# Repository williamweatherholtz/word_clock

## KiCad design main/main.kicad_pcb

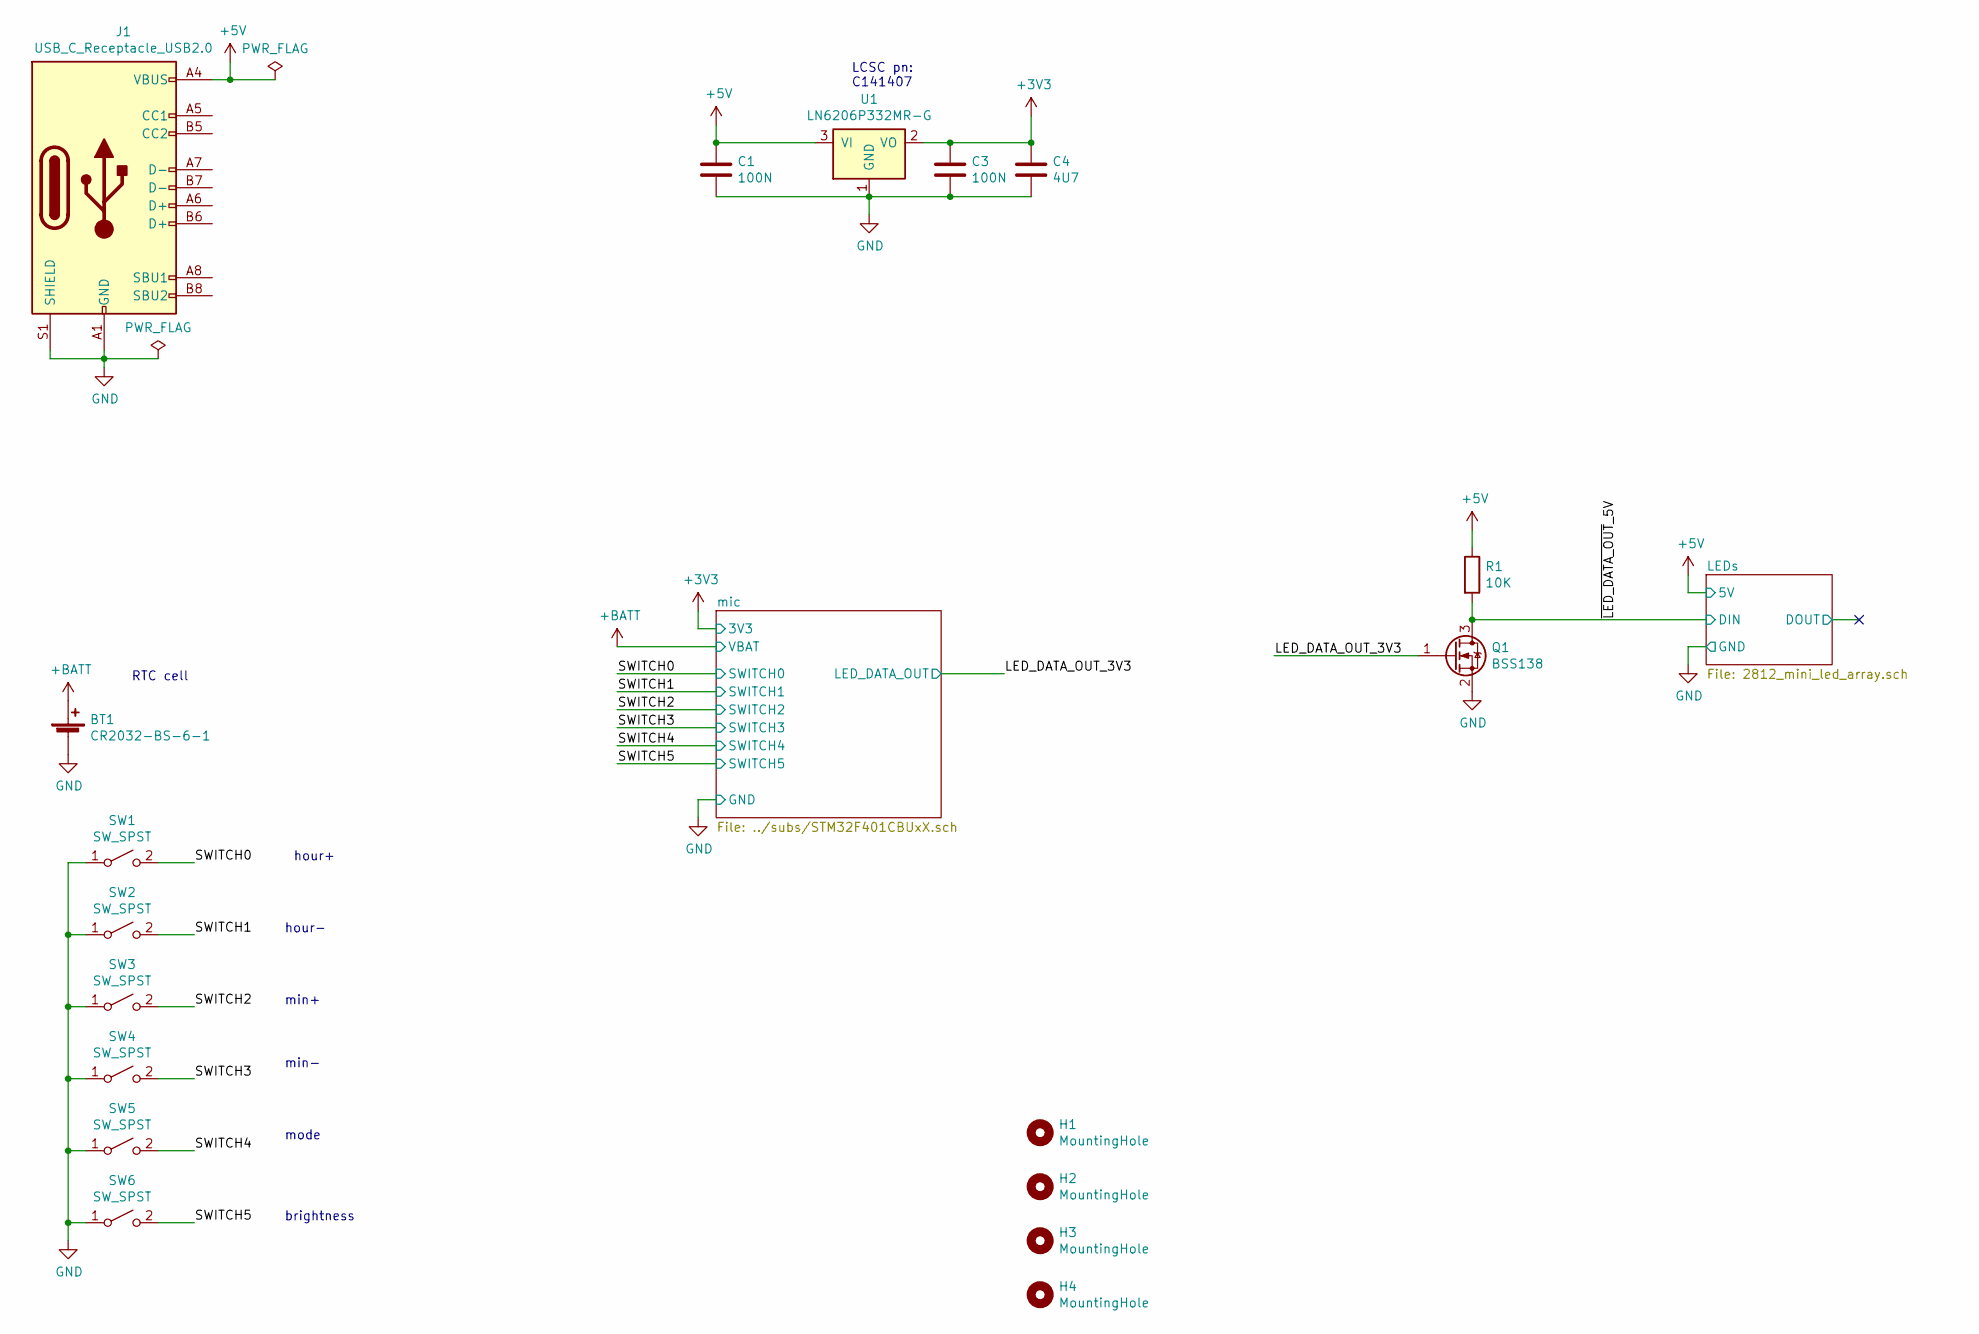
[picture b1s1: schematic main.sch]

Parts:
BT1: CR2032-BS-6-1
C1, C3: 100N; C_0402_1005Metric
C4: 4U7; C_0402_1005Metric
H1, H2, H3, H4: MountingHole; MountingHole_2.1mm
J1: USB_C_Receptacle_USB2.0; C168688
Q1: BSS138; SOT-23
R1: 10K; R_0402_1005Metric
SW1, SW2, SW3, SW4, SW5, SW6: SW_SPST; KAN4562-0501C
U1: LN6206P332MR-G; SOT-23

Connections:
+3V3: C3.1, C4.1, U1.2 (VO); also elsewhere on the board
+5V: C1.1, J1.A4 (VBUS), J1.A9 (VBUS), J1.B4 (VBUS), J1.B9 (VBUS), R1.1, U1.3 (VI); also elsewhere on the board
+BATT: BT1.1 (+); also elsewhere on the board
/LED_DATA_OUT_3V3: Q1.1 (G); also elsewhere on the board
/SWITCH0: SW1.2 (B); also elsewhere on the board
/SWITCH1: SW2.2 (B); also elsewhere on the board
/SWITCH2: SW3.2 (B); also elsewhere on the board
/SWITCH3: SW4.2 (B); also elsewhere on the board
/SWITCH4: SW5.2 (B); also elsewhere on the board
/SWITCH5: SW6.2 (B); also elsewhere on the board
/~LED_DATA_OUT~_5V: Q1.3 (D), R1.2; also elsewhere on the board
GND: BT1.2 (-), C1.2, C3.2, C4.2, J1.A1 (GND), J1.A12 (GND), J1.B1 (GND), J1.B12 (GND), J1.S1 (SHIELD), Q1.2 (S), SW1.1 (A), SW2.1 (A), SW3.1 (A), SW4.1 (A), SW5.1 (A), SW6.1 (A), U1.1 (GND); also elsewhere on the board

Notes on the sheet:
hour+
min+
mode
brightness
hour-
min-
LCSC pn: C141407
RTC cell

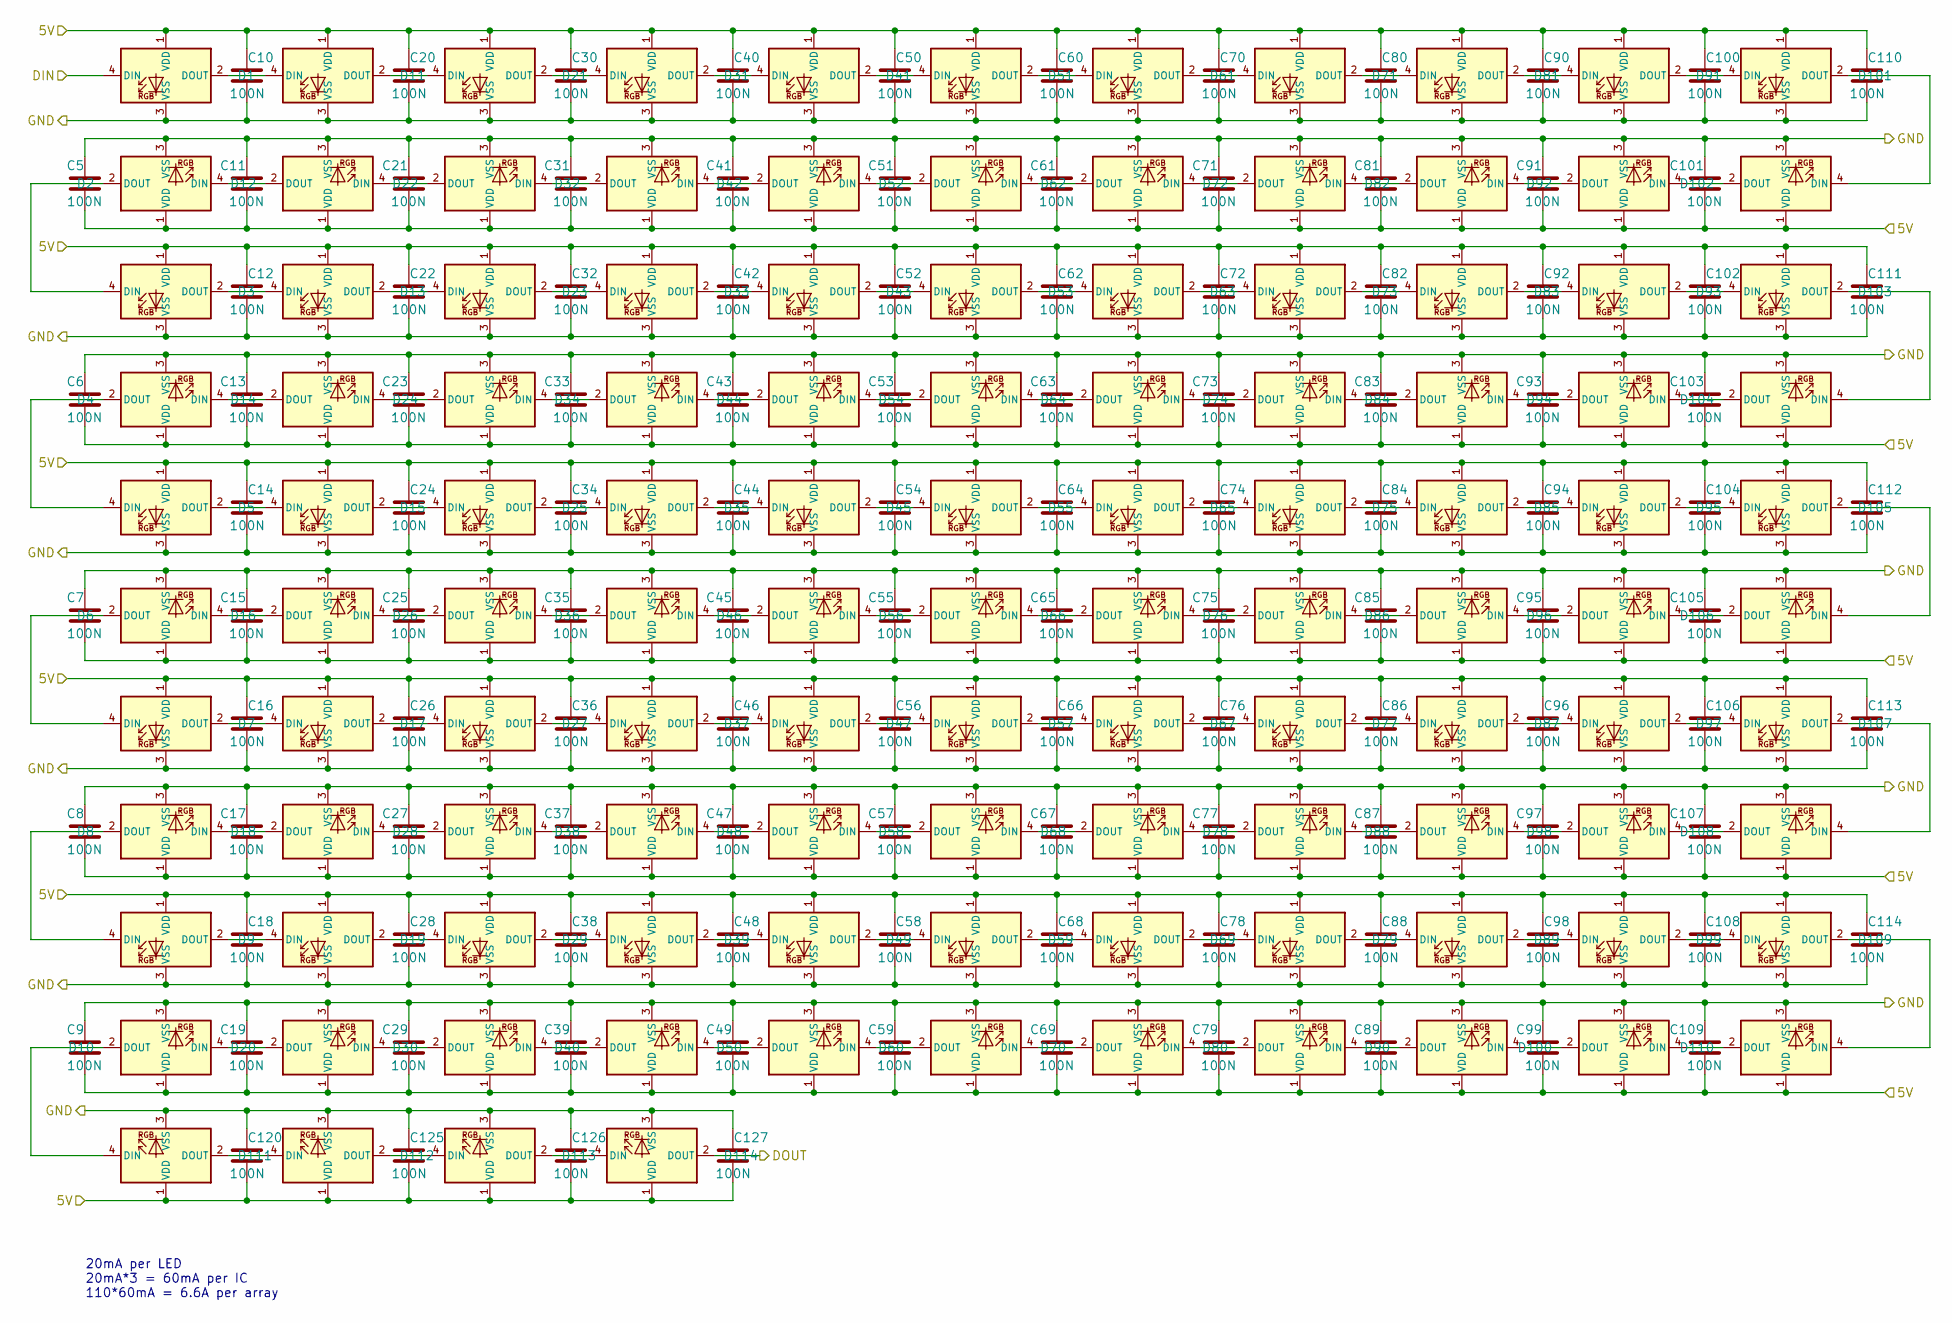
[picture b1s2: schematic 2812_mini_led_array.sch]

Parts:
C5, C6, C7, C8, C9, C10, C11, C12, C13, C14, C15, C16, C17, C18, C19, C20, C21, C22, C23, C24, C25, C26, C27, C28, C29, C30, C31, C32, C33, C34, C35, C36, C37, C38, C39, C40, C41, C42, C43, C44, C45, C46, C47, C48, C49, C50, C51, C52, C53, C54, C55, C56, C57, C58, C59, C60, C61, C62, C63, C64, C65, C66, C67, C68, C69, C70, C71, C72, C73, C74, C75, C76, C77, C78, C79, C80, C81, C82, C83, C84, C85, C86, C87, C88, C89, C90, C91, C92, C93, C94, C95, C96, C97, C98, C99, C100, C101, C102, C103, C104, C105, C106, C107, C108, C109, C110, C111, C112, C113, C114, C120, C125, C126, C127: 100N; C_0402_1005Metric
D1, D2, D3, D4, D5, D6, D7, D8, D9, D10, D11, D12, D13, D14, D15, D16, D17, D18, D19, D20, D21, D22, D23, D24, D25, D26, D27, D28, D29, D30, D31, D32, D33, D34, D35, D36, D37, D38, D39, D40, D41, D42, D43, D44, D45, D46, D47, D48, D49, D50, D51, D52, D53, D54, D55, D56, D57, D58, D59, D60, D61, D62, D63, D64, D65, D66, D67, D68, D69, D70, D71, D72, D73, D74, D75, D76, D77, D78, D79, D80, D81, D82, D83, D84, D85, D86, D87, D88, D89, D90, D91, D92, D93, D94, D95, D96, D97, D98, D99, D100, D101, D102, D103, D104, D105, D106, D107, D108, D109, D110, D111, D112, D113, D114: WS2812B-MINI; WS2812B_v3-MINI

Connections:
+5V: C5.2, C6.2, C7.2, C8.2, C9.2, C10.1, C11.2, C12.1, C13.2, C14.1, C15.2, C16.1, C17.2, C18.1, C19.2, C20.1, C21.2, C22.1, C23.2, C24.1, C25.2, C26.1, C27.2, C28.1, C29.2, C30.1, C31.2, C32.1, C33.2, C34.1, C35.2, C36.1, C37.2, C38.1, C39.2, C40.1, C41.2, C42.1, C43.2, C44.1, C45.2, C46.1, C47.2, C48.1, C49.2, C50.1, C51.2, C52.1, C53.2, C54.1, C55.2, C56.1, C57.2, C58.1, C59.2, C60.1, C61.2, C62.1, C63.2, C64.1, C65.2, C66.1, C67.2, C68.1, C69.2, C70.1, C71.2, C72.1, C73.2, C74.1, C75.2, C76.1, C77.2, C78.1, C79.2, C80.1, C81.2, C82.1, C83.2, C84.1, C85.2, C86.1, C87.2, C88.1, C89.2, C90.1, C91.2, C92.1, C93.2, C94.1, C95.2, C96.1, C97.2, C98.1, C99.2, C100.1, C101.2, C102.1, C103.2, C104.1, C105.2, C106.1, C107.2, C108.1, C109.2, C110.1, C111.1, C112.1, C113.1, C114.1, C120.2, C125.2, C126.2, C127.2, D1.1 (VDD), D2.1 (VDD), D3.1 (VDD), D4.1 (VDD), D5.1 (VDD), D6.1 (VDD), D7.1 (VDD), D8.1 (VDD), D9.1 (VDD), D10.1 (VDD), D11.1 (VDD), D12.1 (VDD), D13.1 (VDD), D14.1 (VDD), D15.1 (VDD), D16.1 (VDD), D17.1 (VDD), D18.1 (VDD), D19.1 (VDD), D20.1 (VDD), D21.1 (VDD), D22.1 (VDD), D23.1 (VDD), D24.1 (VDD), D25.1 (VDD), D26.1 (VDD), D27.1 (VDD), D28.1 (VDD), D29.1 (VDD), D30.1 (VDD), D31.1 (VDD), D32.1 (VDD), D33.1 (VDD), D34.1 (VDD), D35.1 (VDD), D36.1 (VDD), D37.1 (VDD), D38.1 (VDD), D39.1 (VDD), D40.1 (VDD), D41.1 (VDD), D42.1 (VDD), D43.1 (VDD), D44.1 (VDD), D45.1 (VDD), D46.1 (VDD), D47.1 (VDD), D48.1 (VDD), D49.1 (VDD), D50.1 (VDD), D51.1 (VDD), D52.1 (VDD), D53.1 (VDD), D54.1 (VDD), D55.1 (VDD), D56.1 (VDD), D57.1 (VDD), D58.1 (VDD), D59.1 (VDD), D60.1 (VDD), D61.1 (VDD), D62.1 (VDD), D63.1 (VDD), D64.1 (VDD), D65.1 (VDD), D66.1 (VDD), D67.1 (VDD), D68.1 (VDD), D69.1 (VDD), D70.1 (VDD), D71.1 (VDD), D72.1 (VDD), D73.1 (VDD), D74.1 (VDD), D75.1 (VDD), D76.1 (VDD), D77.1 (VDD), D78.1 (VDD), D79.1 (VDD), D80.1 (VDD), D81.1 (VDD), D82.1 (VDD), D83.1 (VDD), D84.1 (VDD), D85.1 (VDD), D86.1 (VDD), D87.1 (VDD), D88.1 (VDD), D89.1 (VDD), D90.1 (VDD), D91.1 (VDD), D92.1 (VDD), D93.1 (VDD), D94.1 (VDD), D95.1 (VDD), D96.1 (VDD), D97.1 (VDD), D98.1 (VDD), D99.1 (VDD), D100.1 (VDD), D101.1 (VDD), D102.1 (VDD), D103.1 (VDD), D104.1 (VDD), D105.1 (VDD), D106.1 (VDD), D107.1 (VDD), D108.1 (VDD), D109.1 (VDD), D110.1 (VDD), D111.1 (VDD), D112.1 (VDD), D113.1 (VDD), D114.1 (VDD); also elsewhere on the board
/~LED_DATA_OUT~_5V: D1.4 (DIN); also elsewhere on the board
GND: C5.1, C6.1, C7.1, C8.1, C9.1, C10.2, C11.1, C12.2, C13.1, C14.2, C15.1, C16.2, C17.1, C18.2, C19.1, C20.2, C21.1, C22.2, C23.1, C24.2, C25.1, C26.2, C27.1, C28.2, C29.1, C30.2, C31.1, C32.2, C33.1, C34.2, C35.1, C36.2, C37.1, C38.2, C39.1, C40.2, C41.1, C42.2, C43.1, C44.2, C45.1, C46.2, C47.1, C48.2, C49.1, C50.2, C51.1, C52.2, C53.1, C54.2, C55.1, C56.2, C57.1, C58.2, C59.1, C60.2, C61.1, C62.2, C63.1, C64.2, C65.1, C66.2, C67.1, C68.2, C69.1, C70.2, C71.1, C72.2, C73.1, C74.2, C75.1, C76.2, C77.1, C78.2, C79.1, C80.2, C81.1, C82.2, C83.1, C84.2, C85.1, C86.2, C87.1, C88.2, C89.1, C90.2, C91.1, C92.2, C93.1, C94.2, C95.1, C96.2, C97.1, C98.2, C99.1, C100.2, C101.1, C102.2, C103.1, C104.2, C105.1, C106.2, C107.1, C108.2, C109.1, C110.2, C111.2, C112.2, C113.2, C114.2, C120.1, C125.1, C126.1, C127.1, D1.3 (VSS), D2.3 (VSS), D3.3 (VSS), D4.3 (VSS), D5.3 (VSS), D6.3 (VSS), D7.3 (VSS), D8.3 (VSS), D9.3 (VSS), D10.3 (VSS), D11.3 (VSS), D12.3 (VSS), D13.3 (VSS), D14.3 (VSS), D15.3 (VSS), D16.3 (VSS), D17.3 (VSS), D18.3 (VSS), D19.3 (VSS), D20.3 (VSS), D21.3 (VSS), D22.3 (VSS), D23.3 (VSS), D24.3 (VSS), D25.3 (VSS), D26.3 (VSS), D27.3 (VSS), D28.3 (VSS), D29.3 (VSS), D30.3 (VSS), D31.3 (VSS), D32.3 (VSS), D33.3 (VSS), D34.3 (VSS), D35.3 (VSS), D36.3 (VSS), D37.3 (VSS), D38.3 (VSS), D39.3 (VSS), D40.3 (VSS), D41.3 (VSS), D42.3 (VSS), D43.3 (VSS), D44.3 (VSS), D45.3 (VSS), D46.3 (VSS), D47.3 (VSS), D48.3 (VSS), D49.3 (VSS), D50.3 (VSS), D51.3 (VSS), D52.3 (VSS), D53.3 (VSS), D54.3 (VSS), D55.3 (VSS), D56.3 (VSS), D57.3 (VSS), D58.3 (VSS), D59.3 (VSS), D60.3 (VSS), D61.3 (VSS), D62.3 (VSS), D63.3 (VSS), D64.3 (VSS), D65.3 (VSS), D66.3 (VSS), D67.3 (VSS), D68.3 (VSS), D69.3 (VSS), D70.3 (VSS), D71.3 (VSS), D72.3 (VSS), D73.3 (VSS), D74.3 (VSS), D75.3 (VSS), D76.3 (VSS), D77.3 (VSS), D78.3 (VSS), D79.3 (VSS), D80.3 (VSS), D81.3 (VSS), D82.3 (VSS), D83.3 (VSS), D84.3 (VSS), D85.3 (VSS), D86.3 (VSS), D87.3 (VSS), D88.3 (VSS), D89.3 (VSS), D90.3 (VSS), D91.3 (VSS), D92.3 (VSS), D93.3 (VSS), D94.3 (VSS), D95.3 (VSS), D96.3 (VSS), D97.3 (VSS), D98.3 (VSS), D99.3 (VSS), D100.3 (VSS), D101.3 (VSS), D102.3 (VSS), D103.3 (VSS), D104.3 (VSS), D105.3 (VSS), D106.3 (VSS), D107.3 (VSS), D108.3 (VSS), D109.3 (VSS), D110.3 (VSS), D111.3 (VSS), D112.3 (VSS), D113.3 (VSS), D114.3 (VSS); also elsewhere on the board
unnamed: D1.2 (DOUT), D11.4 (DIN)
unnamed: D2.2 (DOUT), D3.4 (DIN)
unnamed: D4.2 (DOUT), D5.4 (DIN)
unnamed: D6.2 (DOUT), D7.4 (DIN)
unnamed: D8.2 (DOUT), D9.4 (DIN)
unnamed: D10.2 (DOUT), D111.4 (DIN)
unnamed: D10.4 (DIN), D20.2 (DOUT)
unnamed: D11.2 (DOUT), D21.4 (DIN)
unnamed: D2.4 (DIN), D12.2 (DOUT)
unnamed: D12.4 (DIN), D22.2 (DOUT)
unnamed: D13.2 (DOUT), D23.4 (DIN)
unnamed: D3.2 (DOUT), D13.4 (DIN)
unnamed: D4.4 (DIN), D14.2 (DOUT)
unnamed: D14.4 (DIN), D24.2 (DOUT)
unnamed: D15.2 (DOUT), D25.4 (DIN)
unnamed: D5.2 (DOUT), D15.4 (DIN)
unnamed: D6.4 (DIN), D16.2 (DOUT)
unnamed: D16.4 (DIN), D26.2 (DOUT)
unnamed: D17.2 (DOUT), D27.4 (DIN)
unnamed: D7.2 (DOUT), D17.4 (DIN)
unnamed: D8.4 (DIN), D18.2 (DOUT)
unnamed: D18.4 (DIN), D28.2 (DOUT)
unnamed: D19.2 (DOUT), D29.4 (DIN)
unnamed: D9.2 (DOUT), D19.4 (DIN)
unnamed: D20.4 (DIN), D30.2 (DOUT)
unnamed: D21.2 (DOUT), D31.4 (DIN)
unnamed: D22.4 (DIN), D32.2 (DOUT)
unnamed: D23.2 (DOUT), D33.4 (DIN)
unnamed: D24.4 (DIN), D34.2 (DOUT)
unnamed: D25.2 (DOUT), D35.4 (DIN)
unnamed: D26.4 (DIN), D36.2 (DOUT)
unnamed: D27.2 (DOUT), D37.4 (DIN)
unnamed: D28.4 (DIN), D38.2 (DOUT)
unnamed: D29.2 (DOUT), D39.4 (DIN)
unnamed: D30.4 (DIN), D40.2 (DOUT)
unnamed: D31.2 (DOUT), D41.4 (DIN)
unnamed: D32.4 (DIN), D42.2 (DOUT)
unnamed: D33.2 (DOUT), D43.4 (DIN)
unnamed: D34.4 (DIN), D44.2 (DOUT)
unnamed: D35.2 (DOUT), D45.4 (DIN)
unnamed: D36.4 (DIN), D46.2 (DOUT)
unnamed: D37.2 (DOUT), D47.4 (DIN)
unnamed: D38.4 (DIN), D48.2 (DOUT)
unnamed: D39.2 (DOUT), D49.4 (DIN)
unnamed: D40.4 (DIN), D50.2 (DOUT)
unnamed: D41.2 (DOUT), D51.4 (DIN)
unnamed: D42.4 (DIN), D52.2 (DOUT)
unnamed: D43.2 (DOUT), D53.4 (DIN)
unnamed: D44.4 (DIN), D54.2 (DOUT)
unnamed: D45.2 (DOUT), D55.4 (DIN)
unnamed: D46.4 (DIN), D56.2 (DOUT)
unnamed: D47.2 (DOUT), D57.4 (DIN)
unnamed: D48.4 (DIN), D58.2 (DOUT)
unnamed: D49.2 (DOUT), D59.4 (DIN)
unnamed: D50.4 (DIN), D60.2 (DOUT)
unnamed: D51.2 (DOUT), D61.4 (DIN)
unnamed: D52.4 (DIN), D62.2 (DOUT)
unnamed: D53.2 (DOUT), D63.4 (DIN)
unnamed: D54.4 (DIN), D64.2 (DOUT)
unnamed: D55.2 (DOUT), D65.4 (DIN)
unnamed: D56.4 (DIN), D66.2 (DOUT)
unnamed: D57.2 (DOUT), D67.4 (DIN)
unnamed: D58.4 (DIN), D68.2 (DOUT)
unnamed: D59.2 (DOUT), D69.4 (DIN)
unnamed: D60.4 (DIN), D70.2 (DOUT)
unnamed: D61.2 (DOUT), D71.4 (DIN)
unnamed: D62.4 (DIN), D72.2 (DOUT)
unnamed: D63.2 (DOUT), D73.4 (DIN)
unnamed: D64.4 (DIN), D74.2 (DOUT)
unnamed: D65.2 (DOUT), D75.4 (DIN)
unnamed: D66.4 (DIN), D76.2 (DOUT)
unnamed: D67.2 (DOUT), D77.4 (DIN)
unnamed: D68.4 (DIN), D78.2 (DOUT)
unnamed: D69.2 (DOUT), D79.4 (DIN)
unnamed: D70.4 (DIN), D80.2 (DOUT)
unnamed: D71.2 (DOUT), D81.4 (DIN)
unnamed: D72.4 (DIN), D82.2 (DOUT)
unnamed: D73.2 (DOUT), D83.4 (DIN)
unnamed: D74.4 (DIN), D84.2 (DOUT)
unnamed: D75.2 (DOUT), D85.4 (DIN)
unnamed: D76.4 (DIN), D86.2 (DOUT)
unnamed: D77.2 (DOUT), D87.4 (DIN)
unnamed: D78.4 (DIN), D88.2 (DOUT)
unnamed: D79.2 (DOUT), D89.4 (DIN)
unnamed: D80.4 (DIN), D90.2 (DOUT)
unnamed: D81.2 (DOUT), D91.4 (DIN)
unnamed: D82.4 (DIN), D92.2 (DOUT)
unnamed: D83.2 (DOUT), D93.4 (DIN)
unnamed: D84.4 (DIN), D94.2 (DOUT)
unnamed: D85.2 (DOUT), D95.4 (DIN)
unnamed: D86.4 (DIN), D96.2 (DOUT)
unnamed: D87.2 (DOUT), D97.4 (DIN)
unnamed: D88.4 (DIN), D98.2 (DOUT)
unnamed: D89.2 (DOUT), D99.4 (DIN)
unnamed: D90.4 (DIN), D100.2 (DOUT)
unnamed: D100.4 (DIN), D110.2 (DOUT)
unnamed: D101.2 (DOUT), D102.4 (DIN)
unnamed: D91.2 (DOUT), D101.4 (DIN)
unnamed: D92.4 (DIN), D102.2 (DOUT)
unnamed: D103.2 (DOUT), D104.4 (DIN)
unnamed: D93.2 (DOUT), D103.4 (DIN)
unnamed: D94.4 (DIN), D104.2 (DOUT)
unnamed: D105.2 (DOUT), D106.4 (DIN)
unnamed: D95.2 (DOUT), D105.4 (DIN)
unnamed: D96.4 (DIN), D106.2 (DOUT)
unnamed: D107.2 (DOUT), D108.4 (DIN)
unnamed: D97.2 (DOUT), D107.4 (DIN)
unnamed: D98.4 (DIN), D108.2 (DOUT)
unnamed: D109.2 (DOUT), D110.4 (DIN)
unnamed: D99.2 (DOUT), D109.4 (DIN)
unnamed: D111.2 (DOUT), D112.4 (DIN)
unnamed: D112.2 (DOUT), D113.4 (DIN)
unnamed: D113.2 (DOUT), D114.4 (DIN)

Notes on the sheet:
20mA per LED 20mA*3 = 60mA per IC 110*60mA = 6.6A per array

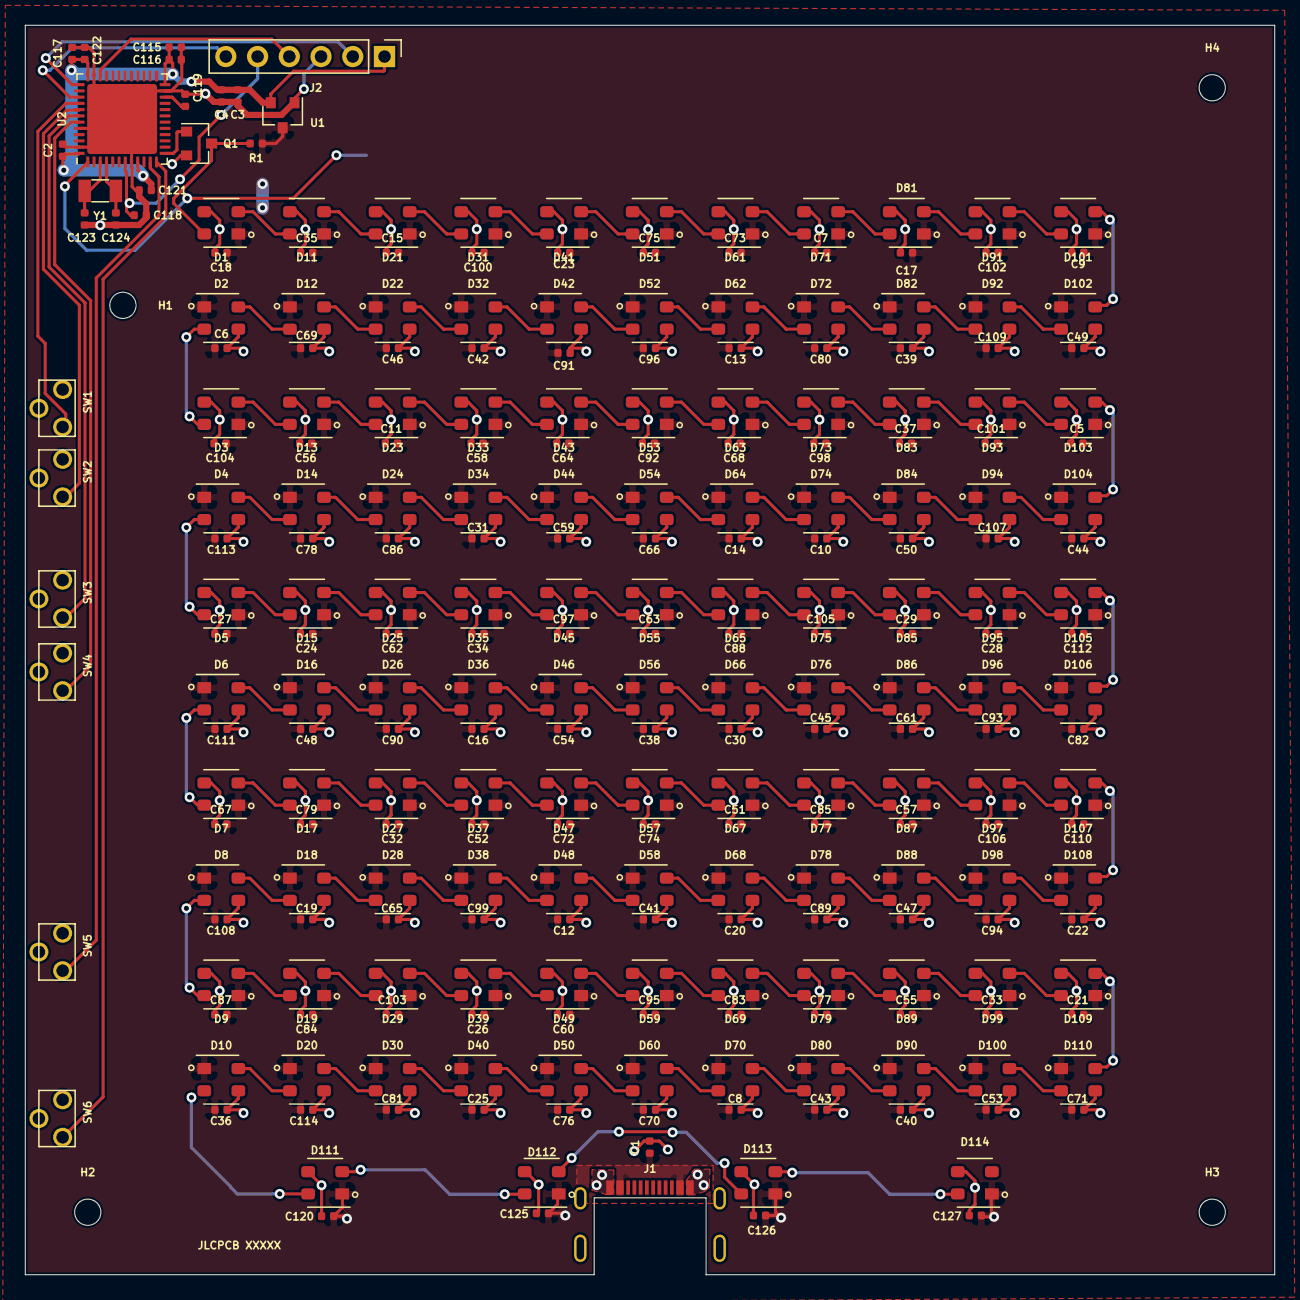
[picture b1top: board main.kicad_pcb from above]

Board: 2 copper layers, 100.0 x 100.0 mm, 259 parts (1 on the bottom side), 132 nets.

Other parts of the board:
C2, C116, C117, C118, C121, C122: 100N; C_0402_1005Metric
C115, C119: 4U7; C_0402_1005Metric
C123, C124: 21P; C_0402_1005Metric
J2: SWD; PinHeader_1x06_P2.54mm_Vertical
U2: STM32F401CBUx; QFN-48-1EP_7x7mm_P0.5mm_EP5.6x5.6mm
Y1: Crystal; Crystal_SMD_3215-2Pin_3.2x1.5mm

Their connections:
+3V3: C2.1, C115.1, C116.1, C117.1, C121.1, C122.1, J2.1, U2.9, U2.24, U2.36, U2.48; also elsewhere on the board
+BATT: U2.1; also elsewhere on the board
/LED_DATA_OUT_3V3: U2.13; also elsewhere on the board
/SWITCH0: U2.40; also elsewhere on the board
/SWITCH1: U2.41; also elsewhere on the board
/SWITCH2: U2.42; also elsewhere on the board
/SWITCH3: U2.43; also elsewhere on the board
/SWITCH4: U2.11; also elsewhere on the board
/SWITCH5: U2.12; also elsewhere on the board
/mic/OSC_IN: C123.1, U2.3, Y1.1
/mic/OSC_OUT: C124.1, U2.4, Y1.2
/mic/SWCLK: J2.2, U2.37
/mic/SWDIO: J2.4, U2.34
/mic/SWO: J2.6, U2.39
/mic/VCAP1: C119.1, U2.22
/mic/~RST: C118.1, J2.5, U2.7
GND: C2.2, C115.2, C116.2, C117.2, C118.2, C119.2, C121.2, C122.2, C123.2, C124.2, J2.3, U2.8, U2.23, U2.35, U2.44, U2.47, U2.49; also elsewhere on the board

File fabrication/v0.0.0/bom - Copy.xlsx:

Id | Designator | Package | Quantity | Designation | LCSC Part Number | Replacement
1 | J1 | C168688 | 1 | USB_C_Receptacle_USB2.0
2 | R1 | R_0402_1005Metric | 1 | 10K | C25744
3 | Q1 | SOT-23 | 1 | BSS138 | C426569
4 | BT1 | CR2032-BS-6-1 | 1 | CR2032-BS-6-1 | C70377
5 | U1 | SOT-23 | 1 | LN6206P332MR-G | C141407
7 | C122, C121, C117, C116, C3, C2, C1, C114, C113, C112, C111, C110, C109, C108, C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 | C_0402_1005Metric | 117 | 100N | C1525
10 | C115 | C_0402_1005Metric | 1 | 4U7 | C23733
13 | Y1 | Crystal_SMD_3215-2Pin_3.2x1.5mm | 1 | Crystal | C32346
14 | C124, C123 | C_0402_1005Metric | 2 | 20P | C1554
15 | SW6, SW5, SW4, SW3, SW2, SW1 | KAN4562-0501C | 6 | SW_SPST | C231728
16 | U2 | QFN-48-1EP_7x7mm_P0.5mm_EP5.6x5.6mm | 1 | STM32F401CBUx | C118825
17 | D11, D1, D110, D109, D108, D107, D106, D105, D104, D103, D102, D101, D100, D99,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 | WS2813-Mini-3.5mm_x_3.5mm | 110 | WS2813-Mini | C189639 | C114583

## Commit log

2019-12-09 init
2019-12-09 removed old branding
2019-12-09 picked microcontroller - stm32f401RETx, started schematic, made LED array
2019-12-09 started layout to see if practical
2019-12-09 squaring up array to see what spacing is reasonable
2019-12-10 most components
2019-12-11 updated fw - set pins correctly
2019-12-11 started layout. Trying to figure out star power topology into MCU
2019-12-11 most layout finished? not super happy w/ star topology, but not lots of noise from this system, so probably just fine. now to add caps...
2019-12-11 mostly done? reviewing now. Also need to fix/update USB connector
2019-12-11 caps done, added FET for 5V logic to WS2813, reduced trace/space
2019-12-11 v0.0.0 ready to send to fab
2019-12-11 improved WS2813 footprint & updated, moved some ref des, still v0.0.0
2019-12-11 updated fab zip
2019-12-12 made spacer layer, replaces Ws2813 with WS2812, fixed fabrication for v0.0.0, now v0.1.0
2019-12-12 added 4 more leds for minute-specific indicator
2019-12-12 moved caps in to LEDs so they'd fit under hole
2019-12-12 added front face, moved around minute mark LEDs so they were spaced evenly and as close together as possible without interfering with USB
2019-12-12 progress and yet not. trying for v0.2.0, but some issues: letters not aligned, switches to tall, minute leds too close to USB_C
